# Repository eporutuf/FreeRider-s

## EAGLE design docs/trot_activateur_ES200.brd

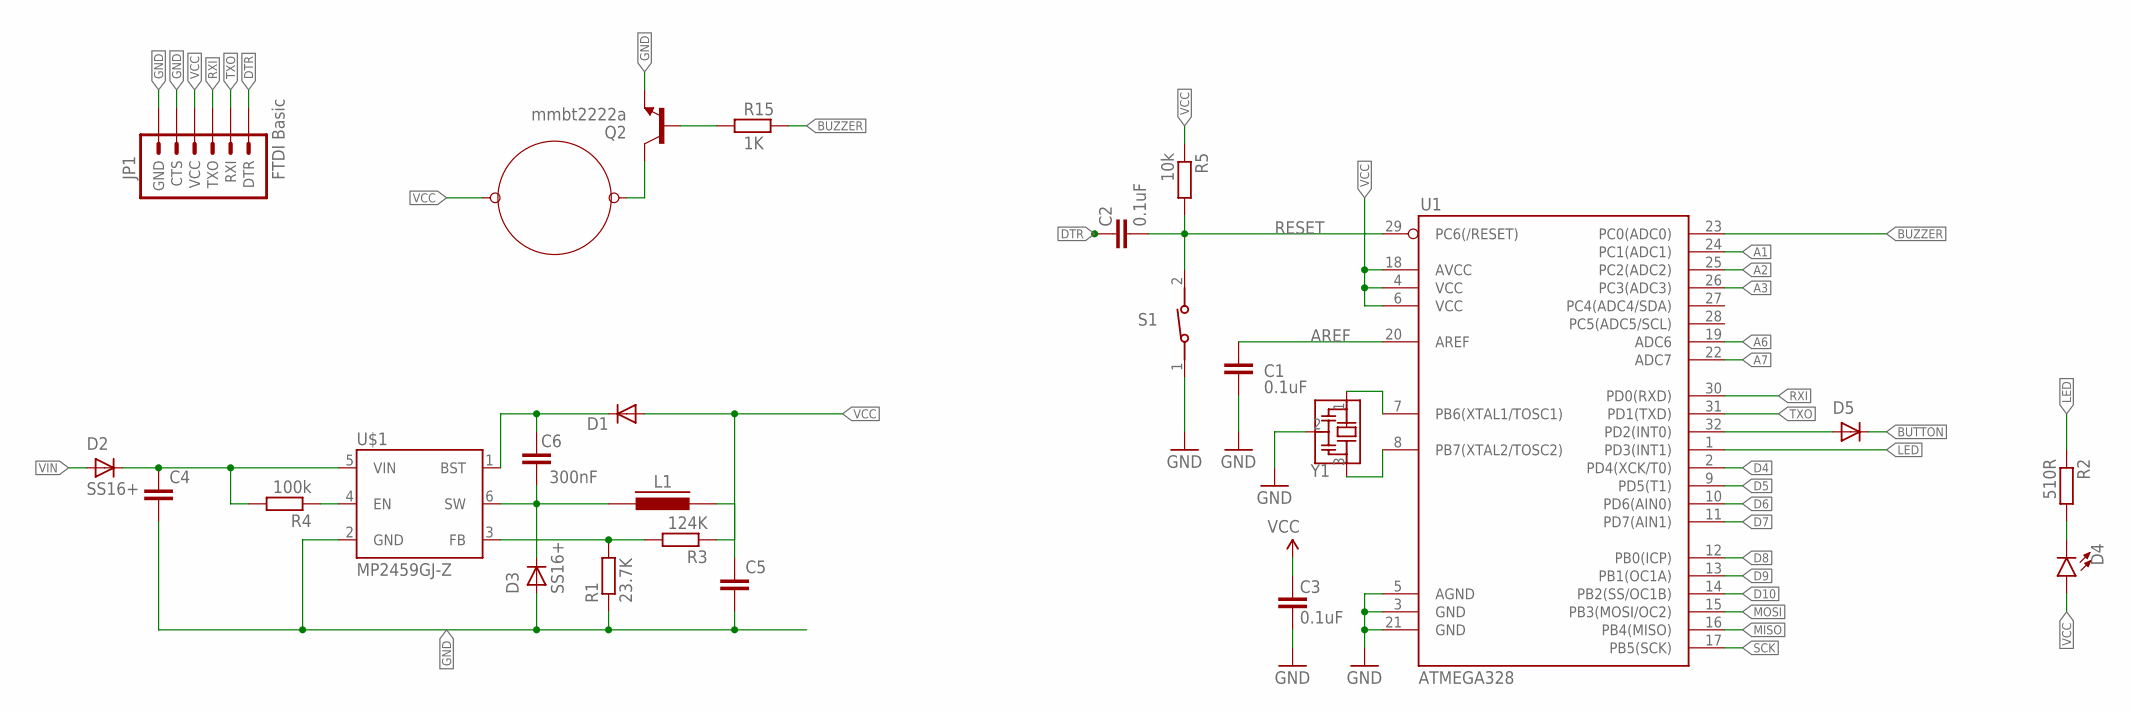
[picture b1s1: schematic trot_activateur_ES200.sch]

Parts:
C1, C2, C3: 0.1uF; C0603
C4: 4.7uF; X7R; 50V; C1210
C5: 22uF;X7R;10V; C1210
C6: 300nF; C0603
D1: 1N4148W RH; SOD123
D2, D3, D5: SS16+; SMA-DO214AC
D4: LED0603; LED-0603
JP1: FTDI Basic; 1X06
L1: VLS5045EX-151M; VLS5045EX
Q2: mmbt2222a; SPARKFUN_SOT23-3
R1: 23.7K; R0603
R2: 510R; R0603
R3: 124K; R0603
R4: 100k; R0603
R5: 10k; R0603
R15: 1K; R0603
S1: 434113025826
U1: ATMEGA328; SPARKFUN_TQFP32-08
U$1: MP2459GJ-Z; SOT23-6
U$6: BUZZER-KPX-G1203UB
Y1: CSTNE16M0V530000R0; OSC_CSTNE16M0V530000R0

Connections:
A1: U1.24 (PC1(ADC1))
A2: U1.25 (PC2(ADC2))
A3: U1.26 (PC3(ADC3))
A6: U1.19 (ADC6)
A7: U1.22 (ADC7)
AREF: C1.2, U1.20 (AREF)
BUTTON: D5.K (C)
BUZZER: R15.2, U1.23 (PC0(ADC0))
D4: U1.2 (PD4(XCK/T0))
D5: U1.9 (PD5(T1))
D6: U1.10 (PD6(AIN0))
D7: U1.11 (PD7(AIN1))
D8: U1.12 (PB0(ICP))
D9: U1.13 (PB1(OC1A))
D10: U1.14 (PB2(SS/OC1B))
DTR: C2.2, JP1.1 (DTR)
GND: C1.1, C3.1, C4.2, C5.2, D3.A, JP1.5 (CTS), JP1.6 (GND), Q2.2 (E), R1.1, S1.1, U1.3 (GND), U1.5 (AGND), U1.21 (GND), U$1.2 (GND), Y1.2 (GND)
LED: R2.1, U1.1 (PD3(INT1))
MISO: U1.16 (PB4(MISO))
MOSI: U1.15 (PB3(MOSI/OC2))
unnamed: U1.8 (PB7(XTAL2/TOSC2)), Y1.3 (OUT)
unnamed: U1.7 (PB6(XTAL1/TOSC1)), Y1.1 (IN)
unnamed: R4.1, U$1.4 (EN)
unnamed: C4.1, D2.K (C), R4.2, U$1.5 (VIN)
unnamed: R1.2, R3.2, U$1.3 (FB)
unnamed: C6.2, D3.K (C), L1.P$1 (1), U$1.6 (SW)
unnamed: C6.1, D1.C, U$1.1 (BST)
unnamed: D4.C, R2.2
unnamed: D5.A, U1.32 (PD2(INT0))
unnamed: Q2.1 (B), R15.1
unnamed: Q2.3 (C), U$6.P$2
RESET: C2.1, R5.2, S1.2, U1.29 (PC6(/RESET))
RXI: JP1.3 (TXO), U1.30 (PD0(RXD))
SCK: U1.17 (PB5(SCK))
TXO: JP1.2 (RXI), U1.31 (PD1(TXD))
VCC: C3.2, C5.1, D1.A, D4.A, JP1.4 (VCC), L1.P$2 (2), R3.1, R5.1, U1.4 (VCC), U1.6 (VCC), U1.18 (AVCC), U$6.P$1
VIN: D2.A

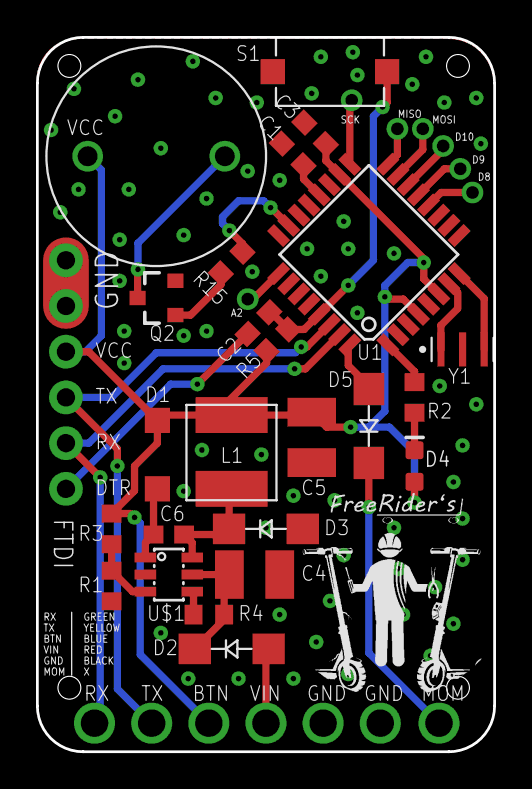
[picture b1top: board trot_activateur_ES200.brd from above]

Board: 2 copper layers, 25.4 x 39.7 mm, 25 parts (1 on the bottom side), 20 nets.

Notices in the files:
parts and their libraries:
switch: Copyright: Würth Elektronik
LED: Licensing: Creative Commons ShareAlike 4.0 International - https://creativecommons.org/licenses/by-sa/4.0
